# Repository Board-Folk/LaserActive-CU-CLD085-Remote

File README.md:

# LaserActive CU-CLD085 Remote Control

This repository contains a recreation of the remote control PCB
for the Laser Active. This recreation was reversed engineering using scanned images of the original
board's copper layers, so should be a reasonably accurate reproduction.

Both THT and SMD caps added, use one or the other.

[**Interactive BOM**][IBOM]

Use board thickness 1.0 mm

[**PCB Gerber**][GERBER]

## Thanks

  * Rob Taylor ([@PeepoUK](https://github.com/PeepoUK)) for doing most of
    the PCB layout
  * Zaxour 阿宅 (@zaxour) for tweaking and testing
  * The rest of the Board Folk Team for their support and general
    coolness.
&nbsp;

## Legal

As the product of this project is a replica of a proprietary product, the
the author makes no claim of copyright to the schematics nor PCB layouts and
releases these into the public domain, solely for the purposes of study and
historical preservation.

You are free to produce PCBs based on this project's designs at your own risk
and without limitation, for your own use or for sale and/or repair at a
reasonable price. Attribution is appreciated. The authors are not obliged to
provide support of any kind.

Under no circumstances will the authors be held responsible or liable in any
way for losses, damages or costs resulting from the use of the information
and/or resources of this project.

The resources are provided "as-is" without warranty of any kind, either
expressed or implied, including, but not limited to, the implied warranties
of merchantability and fitness for a particular purpose.

[IBOM]: http://htmlpreview.github.io/?https://raw.githubusercontent.com/Board-Folk/LaserActive-CU-CLD085-Remote/main/ibom.html

[GERBER]: https://github.com/Board-Folk/LaserActive-CU-CLD085-Remote/raw/refs/heads/main/jlcpcb/production_files/GERBER-LaserActive-CU-CLD085-Remote.zip

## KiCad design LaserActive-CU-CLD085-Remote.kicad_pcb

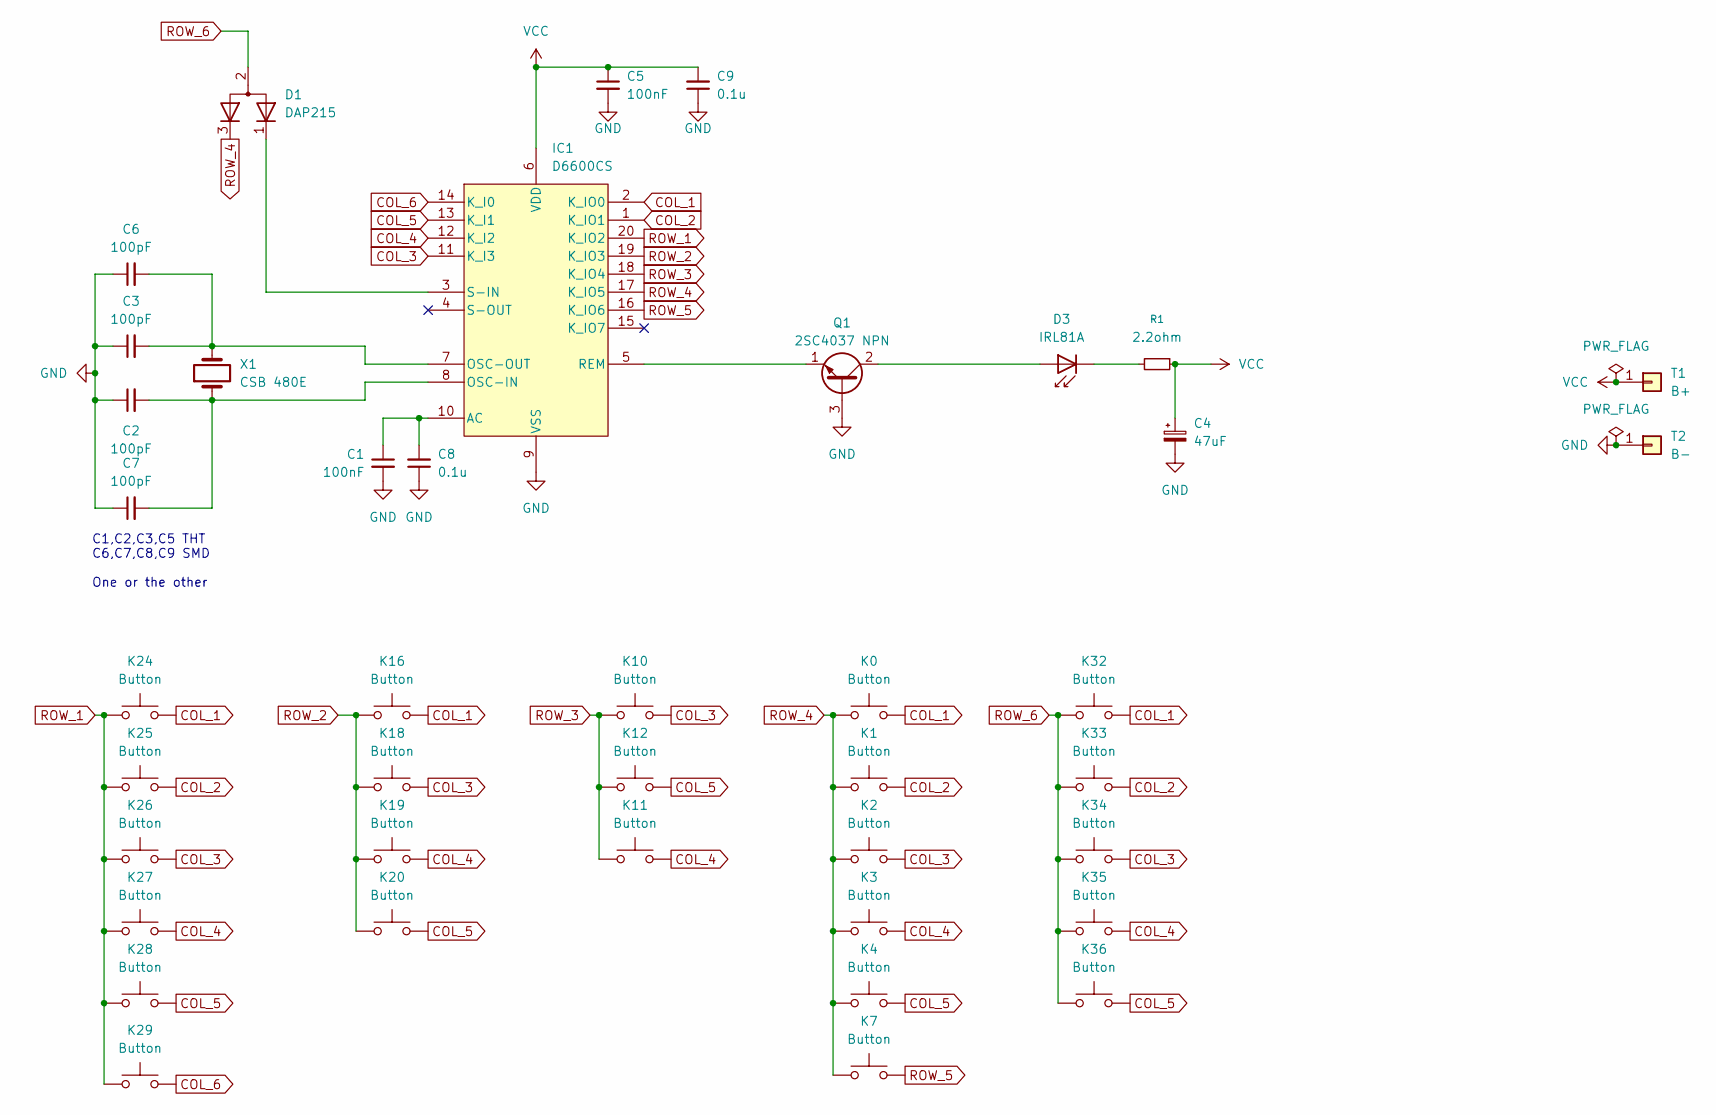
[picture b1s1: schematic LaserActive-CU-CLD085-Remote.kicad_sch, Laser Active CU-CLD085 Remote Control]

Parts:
C1, C5: 100nF; C_Disc_D4.3mm_W1.9mm_P5.00mm
C2, C3: 100pF; C_Disc_D3.0mm_W1.6mm_P2.50mm
C4: 47uF; Electrolytic_P2.50mm
C6, C7: 100pF; C_0603_1608Metric
C8, C9: 0.1u; C_0603_1608Metric
D1: DAP215; TO-126-3_Vertical
D3: IRL81A; LED_SideEmitter_Rectangular_W4.5mm_H1.6mm
IC1: D6600CS; DIP-20_W7.62mm_P1.76mm
K0, K1, K2, K3, K4, K7, K10, K11, K12, K16, K18, K19, K20, K24, K25, K26, K27, K28, K29, K32, K33, K34, K35, K36: Button
Q1: 2SC4037 NPN; TO-220-3
R1: 2.2ohm; R_Axial_DIN0204_L3.6mm_D1.6mm_P5.08mm_Horizontal
T1: B+; Battery Terminal
T2: B-; Battery Terminal
X1: CSB 480E; Crystal

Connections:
COL_1: IC1.2 (K_IO0), K0.2, K16.2, K24.2, K32.2
COL_2: IC1.1 (K_IO1), K1.1, K25.2, K33.1
COL_3: IC1.11 (K_I3), K2.1, K10.2, K18.2, K26.2, K34.2
COL_4: IC1.12 (K_I2), K3.1, K11.1, K19.2, K27.1, K35.2
COL_5: IC1.13 (K_I1), K4.2, K12.2, K20.2, K28.2, K36.1
COL_6: IC1.14 (K_I0), K29.1
GND: C1.2, C2.1, C3.1, C4.2, C5.2, C6.1, C7.1, C8.1, C9.1, IC1.9 (VSS), Q1.3 (B), T2.1 (Pin_1_1)
unnamed: D3.2 (A), Q1.2 (C)
unnamed: D3.1 (K), R1.2
unnamed: C1.1, C8.2, IC1.10 (AC)
unnamed: C2.2, C7.2, IC1.8 (OSC-IN), X1.1
unnamed: C3.2, C6.2, IC1.7 (OSC-OUT), X1.2
unnamed: IC1.5 (REM), Q1.1 (E)
unnamed: D1.1 (K), IC1.3 (S-IN)
ROW_1: IC1.20 (K_IO2), K24.1, K25.1, K26.1, K27.2, K28.1, K29.2
ROW_2: IC1.19 (K_IO3), K16.1, K18.1, K19.1, K20.1
ROW_3: IC1.18 (K_IO4), K10.1, K11.2, K12.1
ROW_4: D1.3 (K), IC1.17 (K_IO5), K0.1, K1.2, K2.2, K3.2, K4.1, K7.2
ROW_5: IC1.16 (K_IO6), K7.1
ROW_6: D1.2 (A), K32.1, K33.2, K34.1, K35.1, K36.2
VCC: C4.1, C5.1, C9.2, IC1.6 (VDD), R1.1, T1.1 (Pin_1_1)

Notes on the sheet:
C1,C2,C3,C5 THT C6,C7,C8,C9 SMD One or the other

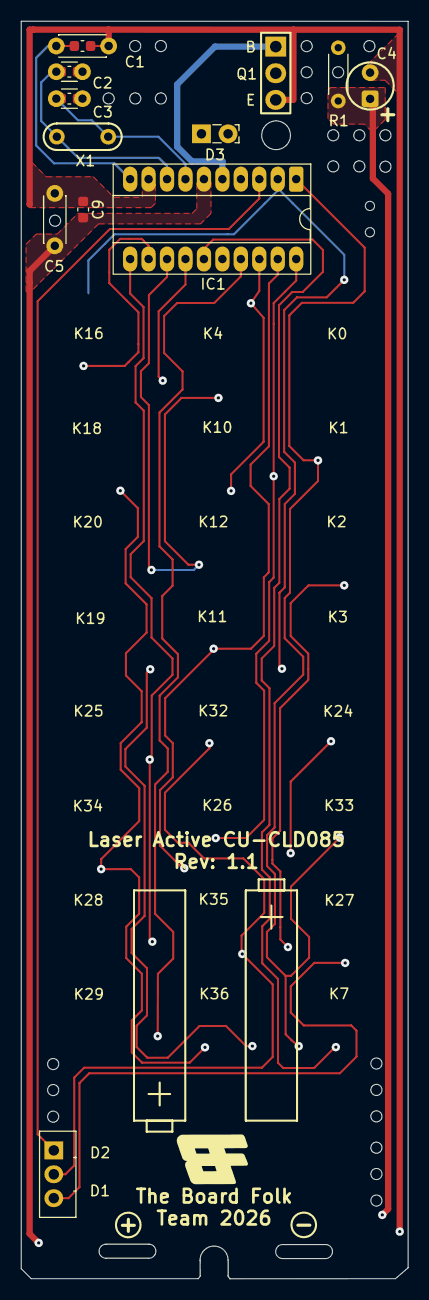
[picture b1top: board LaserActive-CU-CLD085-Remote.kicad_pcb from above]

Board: 2 copper layers, 36.9 x 119.9 mm, 41 parts (0 on the bottom side), 21 nets.

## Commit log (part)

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2026-01-11 Initial start
2026-01-12 Add image with no carbon
2026-01-12 Added no carbon image to pcb
2026-01-17 Update Schematics and PCB
2026-01-17 fix extra b+
2026-01-18 Fix Schematic Values and symbols
2026-01-18 Little Tweaks
2026-01-18 Images
2026-01-18 JLC Gerbers
2026-01-18 Silk Tweaks
2026-01-18 moved images
2026-01-18 BOM & Schematics
